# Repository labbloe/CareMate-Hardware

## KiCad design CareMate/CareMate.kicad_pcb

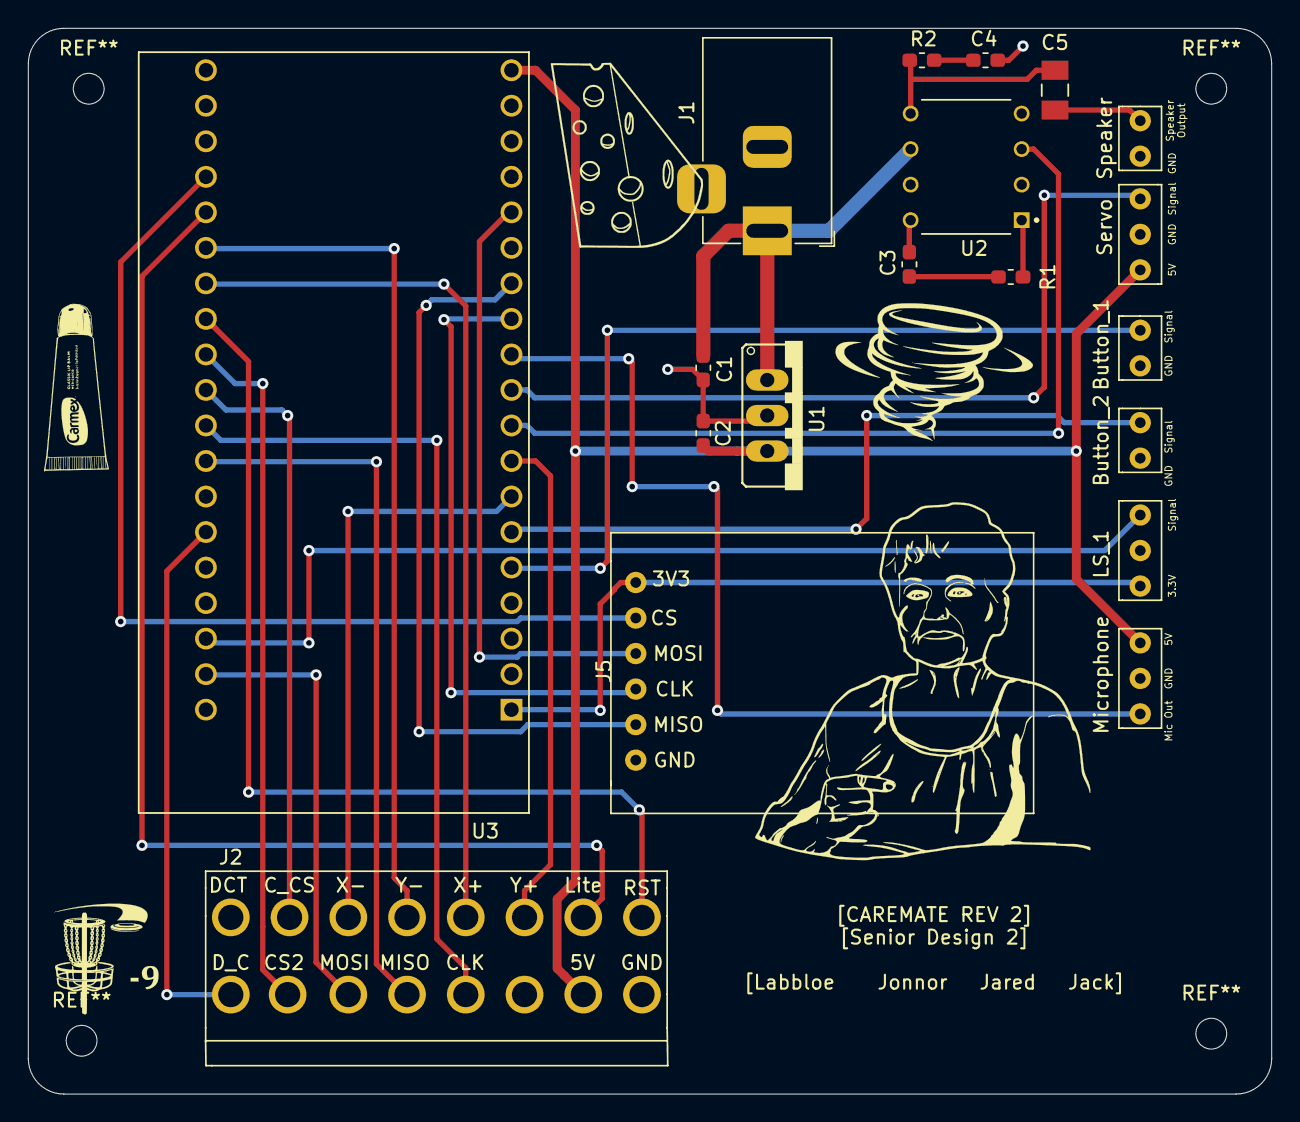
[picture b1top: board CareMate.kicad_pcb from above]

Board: 2 copper layers, 88.9 x 76.2 mm, 19 parts (0 on the bottom side), 32 nets.

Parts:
Button_1, Button_2: Molex_SL_02; Easy_2Pin
C1: 0.33uF; C_0603_1608Metric_Pad1.05x0.95mm_HandSolder
C2: 0.1uF; C_0603_1608Metric_Pad1.05x0.95mm_HandSolder
C3: 10uF; C_0603_1608Metric_Pad1.05x0.95mm_HandSolder
C4: .05uF; C_0603_1608Metric_Pad1.05x0.95mm_HandSolder
C5: 250uF; CAPC3216X190N
J1: Barrel_Jack_MountingPin; BarrelJack_Horizontal
J2: Conn_01x16; 16PinConnector
J5: Conn_01x06; SD_Card_Reader
LS_1: Conn_01x03; Easy_3Pin
Microphone: Conn_01x03; Easy_3Pin
R1: 1.2k; R_0603_1608Metric_Pad1.05x0.95mm_HandSolder
R2: 10; R_0603_1608Metric_Pad1.05x0.95mm_HandSolder
Servo: Conn_01x03; Easy_3Pin
Speaker: Conn_01x02; Easy_2Pin
U1: L7805
U2: LM386; LM386N
U3: ESP32-DEVKITC-32D; MODULE_ESP32-DEVKITC-32D

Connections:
3.3V: J5.1, LS_1.3, U3.1
+5V: C2.2, J2.2, Microphone.1, Servo.1, U1.3, U3.19
+9V: C1.2, J1.1, U1.1, U2.6
Amp_Output: C5.1, Speaker.1
Button_1: Button_1.1, U3.5
Button_2: Button_2.1, U3.6
CS1: J5.2, U3.35
CS2: J2.7, U3.30
Card_CS: J2.15, U3.29
D_C: J2.8, U3.25
GND: Button_1.2, Button_2.2, C1.1, C2.1, C4.1, J1.2, J2.1, J5.6, Microphone.2, Servo.2, Speaker.2, U1.2, U2.2, U2.4, U3.20, U3.26
LS_1: LS_1.1, U3.22
Lite: J2.10, U3.34
MISO1: J5.5, U3.13
MISO2: J2.5, U3.27
MOSI1: J5.3, U3.15
MOSI2: J2.6, U3.21
Mic_Out: Microphone.3, U3.11
unnamed: C3.1, U2.8
unnamed: C3.2, R1.2
unnamed: C4.2, R2.2
unnamed: C5.2, R2.1, U2.5
unnamed: R1.1, U2.1
RST: J2.9, U3.31
Servo_1: Servo.3, U3.10
Unamplified_Signal: U2.3, U3.9
X+: J2.12, U3.32
X-: J2.14, U3.7
Y+: J2.11, U3.8
Y-: J2.13, U3.33
clk1: J5.4, U3.12
clk2: J2.4, U3.28

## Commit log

2021-09-02 Added Schematic
2021-09-09 Began assigning footprints, created new ones
2021-09-09 Updated Footprints
2021-09-13 Finished assigning footprints and generated first netlist
2021-09-13 generated PCB and loaded netlist
2021-09-17 significant PCB modifications including changes to elechouse footprint
2021-09-17 began running traces
2021-09-17 Finished routing traces
2021-09-17 curved edgecuts
2021-09-17 added silkscreens
2021-09-17 fixed unconnected items
2021-09-17 added drill holes
2021-09-17 generated step file
2021-09-17 Created gerber and drill files
2021-10-05 Added stl files
2021-10-05 Archived old files
2021-10-20 Update Case
2021-10-29 PCB second revision
2021-11-03 fixed esp gnd
2021-11-04 fixed schematic
2021-11-04 rearranged board layout
2021-11-04 ran traces
2021-11-04 thruholes
2021-11-04 added mounting holes 2.2mm
2021-11-04 generated gerbs and step
2021-11-05 Added drill files to gerber folder
2021-11-15 Case V2
2021-11-15 Printing Files
2021-12-01 Added v3
